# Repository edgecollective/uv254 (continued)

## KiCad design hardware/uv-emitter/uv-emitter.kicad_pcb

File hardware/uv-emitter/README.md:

# UV-Emitter

UV LED board: an Inolux IN-C35PPCTGU0 UV-C LED with its driver circuit.
Called **UV-LED-source** in the `uv-water` repository.

The driver is a current sink: an OPA4340 op-amp drives Q1 so that the
voltage across R2 (24.9 Ω) matches LED_DRIVE divided down by R3/R4 (100k/24.9k):
3.3 V on LED_DRIVE gives about 26 mA, and 2.5 V about 20 mA. From v0.5 the op-amp runs from 3.3 V, Q1 is an
MMBT3904 (a BSS138 fits the same pads), and the LED has its own 12 V supply.

The cable connector is a 6-pin JST PH (J2), with a 0.1" socket (J1) in
parallel:

| Pin | 1 | 2 | 3 | 4 | 5 | 6 |
|---|---|---|---|---|---|---|
| Signal | LED_CURRENT_MEASURE (`LED_CUR`) | LED_DISABLE (`LED_DIS`) | LED_DRIVE (`LED_DRV`) | +12V (LED supply) | 3V3 | GND |

LED_DISABLE high turns the LED off (Q2 grounds the setpoint). LED_CURRENT_MEASURE
is the voltage across R2: 0.5 V at 20 mA.

Open `uv-emitter.kicad_pro` in KiCad 10. Custom parts come from
[`lib/`](../../lib).

**[Download the KiCad files (zip)](https://github.com/edgecollective/uv254/archive/refs/heads/main.zip)**: the whole repository as it is on
`main`, because the board needs the shared `lib/` folder. This board is in
`hardware/uv-emitter/`.

<!-- render-images:start -->
<!-- Generated by scripts/render-images.sh. Edits between these markers are overwritten. -->

## Schematic

Click the image for the [PDF](docs/uv-emitter-schematic.pdf).

## Board layout

Copper and silkscreen. The back is mirrored, as seen from below.

| Front | Back |
|:---:|:---:|
|  |  |

## 3D view

| Front | Back |
|:---:|:---:|
|  |  |

Images of the current design, made with `scripts/render-images.sh uv-emitter`.
Re-run it after changing the board; see
[Updating the board images](../../README.md#updating-the-board-images).
<!-- render-images:end -->

## Revisions

| Version | Date | Status | Design | Fab files |
|---|---|---|---|---|
| v0.1 | 2024-03-11 | gerbers released | tag `uv-emitter/v0.1` | [`fab/v0.1`](fab/v0.1) |
| v0.2 | 2024-04-06 | gerbers released | tag `uv-emitter/v0.2` | [`fab/v0.2`](fab/v0.2) |
| v0.3 | 2024-08-19 | ordered from JLCPCB with detector v0.3 and control v0.1 | tag `uv-emitter/v0.3` | [`fab/v0.3`](fab/v0.3) |
| v0.2_A | 2026-06 to 2026-10 | design revision branched from v0.2, not fabricated | tag `uv-emitter/v0.2_A` | — |
| v0.4 | 2026-11-08 | gerbers released; derived from v0.2_A (5 V, 7 V LED supply, LED_ENABLE) | tag `uv-emitter/v0.4` | [`fab/v0.4`](fab/v0.4) |
| v0.5 | 2026-11-23 | gerbers released, then renumbered v0.6 with the set before ordering (same design) | tag `uv-emitter/v0.5` | [`fab/v0.5`](fab/v0.5) |
| **v0.6** | 2026-11-23 | **gerbers released**: 3.3 V, 12 V LED supply, MMBT3904 driver, LED_DISABLE; for UV-Control v0.6 | tag `uv-emitter/v0.6` | [`fab/v0.6`](fab/v0.6) |

Notes:

- **v0.3** has no `.kicad_pro`, because it was never committed upstream. Open
  `uv-emitter.kicad_pcb` or `.kicad_sch` directly at that tag.
- **v0.4** was called "v0.3" in `uv-water`. It was renumbered because v0.3 was
  already used by the 2024 JLCPCB order.
- **v0.4 has a pinout error on Q2**, the LED-disable switch. Its symbol was the
  through-hole 2N7000 (pin 1 source, 2 gate, 3 drain) on a SOT-23 footprint,
  where a 2N7002 or BSS138 has pin 1 gate, 2 source, 3 drain. With a SOT-23
  MOSFET fitted, Q2's gate is held at GND and LED_ENABLE drives its source: the
  LED can't be turned off that way, and driving LED_ENABLE high makes Q2's body
  diode conduct, raising the setpoint to about 2.7 V, which asks for about
  100 mA instead of 20 mA. On v0.4 boards, leave Q2 unfitted (or keep
  LED_ENABLE low) and turn the LED off with LED_DRIVE = 0. Fixed in v0.5.
- **v0.5** (in progress) moves to the system-wide 3.3 V supply:
  - op-amp supply 3.3 V instead of 5 V (connector pin 5); the LED gets its own
    12 V supply on pin 4 instead of 7.5 V, for more headroom over the LED's
    forward voltage
  - Q1 is an MMBT3904 NPN with a 1 kΩ base resistor (R1, was a 2N7002-type
    MOSFET with 49.9 Ω), so the 3.3 V op-amp has plenty of drive; a BSS138 fits
    the same pads
  - Q2 uses the 2N7002 symbol, which fixes the v0.4 pinout error
  - LED_ENABLE renamed LED_DISABLE, since high turns the LED off (behaviour
    unchanged)
  - board re-laid out

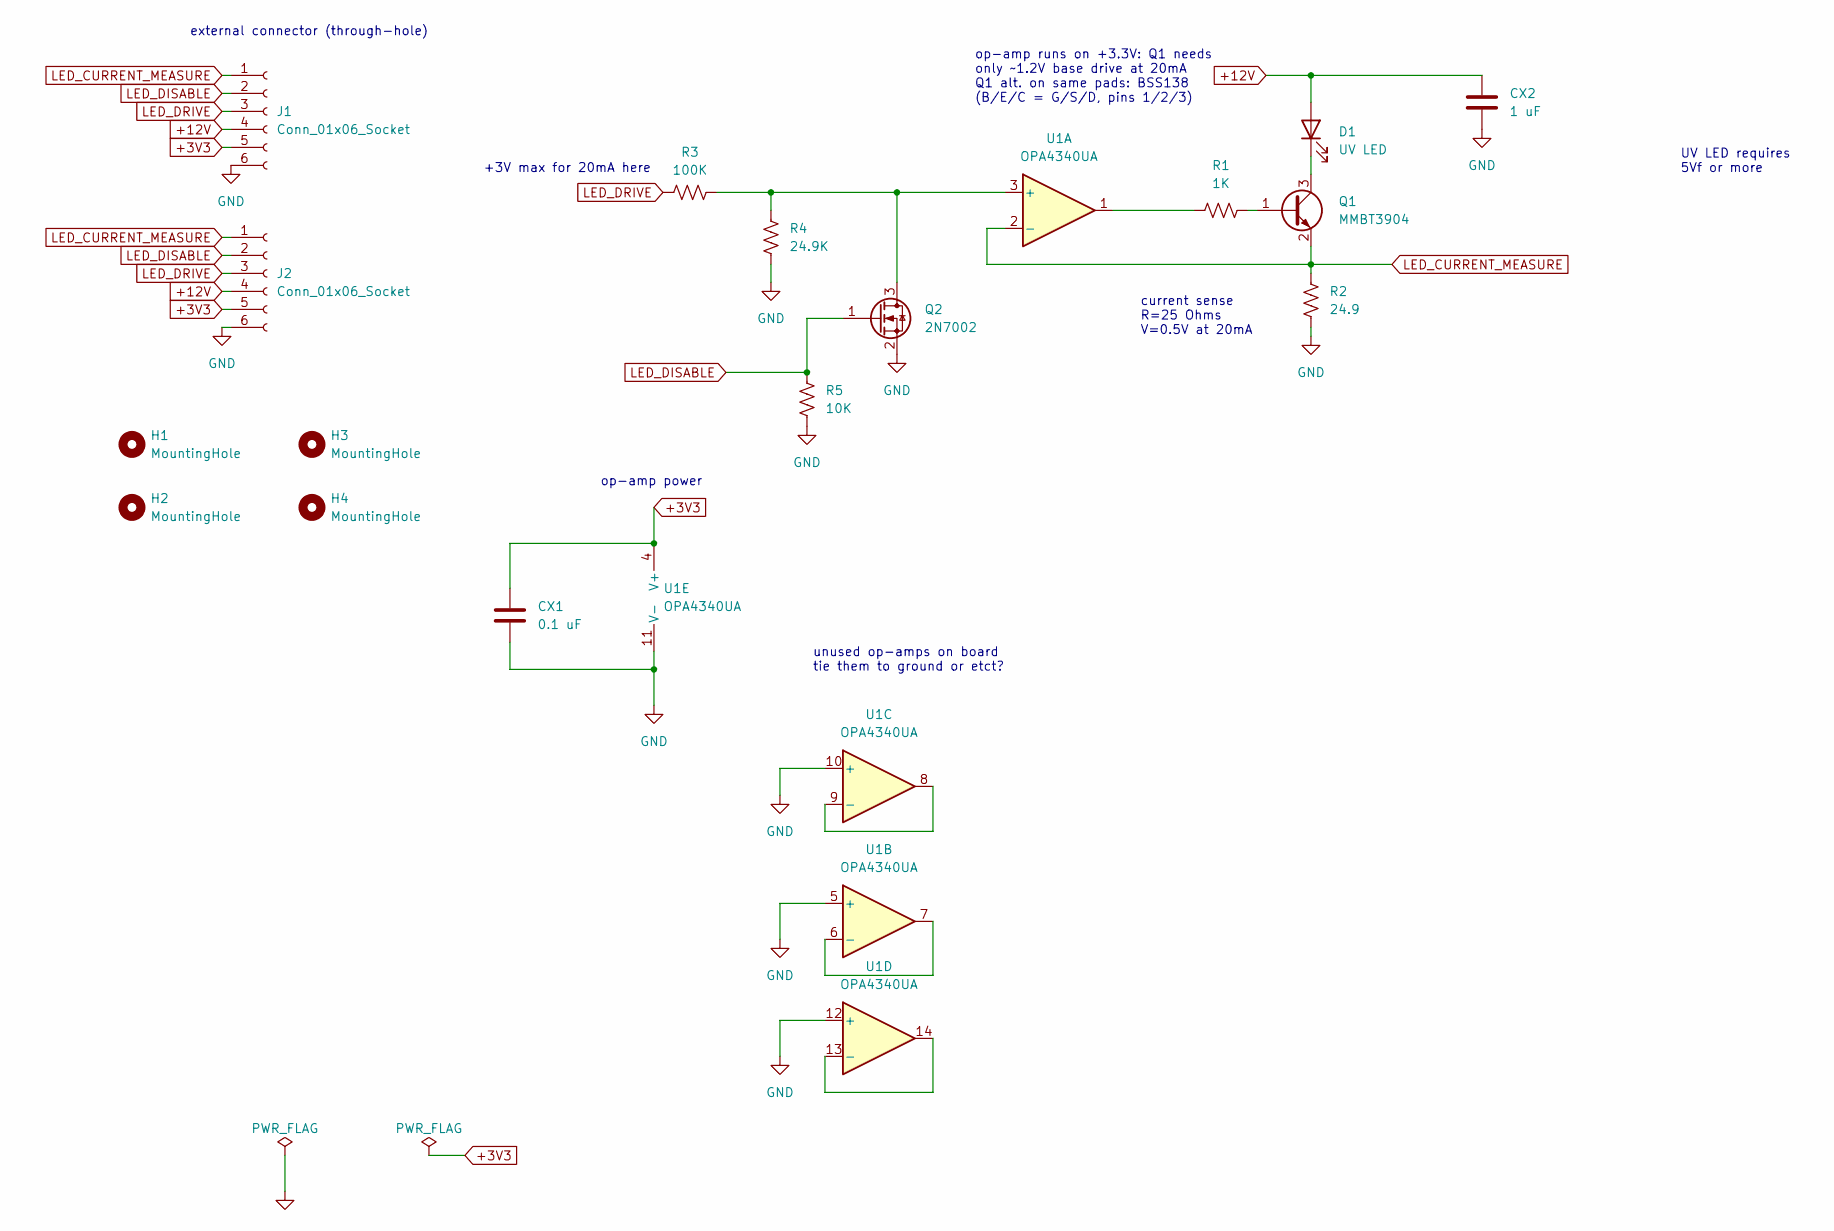
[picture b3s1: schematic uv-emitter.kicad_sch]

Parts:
CX1: 0.1 uF; C_0805_2012Metric_Pad1.18x1.45mm_HandSolder
CX2: 1 uF; C_0805_2012Metric_Pad1.18x1.45mm_HandSolder
D1: UV LED; LED_IN-C35PPCTGU0
H1, H2, H3, H4: MountingHole; MountingHole_3.2mm_M3
J1: Conn_01x06_Socket; PinSocket_1x06_P2.54mm_Vertical
J2: Conn_01x06_Socket; JST_PH_B6B-PH-K_1x06_P2.00mm_Vertical
Q1: MMBT3904; SOT-23
Q2: 2N7002; SOT-23
R1: 1K; R_0805_2012Metric_Pad1.20x1.40mm_HandSolder
R2: 24.9; R_0805_2012Metric_Pad1.20x1.40mm_HandSolder
R3: 100K; R_0805_2012Metric_Pad1.20x1.40mm_HandSolder
R4: 24.9K; R_0805_2012Metric_Pad1.20x1.40mm_HandSolder
R5: 10K; R_0805_2012Metric_Pad1.20x1.40mm_HandSolder
U1: OPA4340UA; SOIC-14_3.9x8.7mm_P1.27mm

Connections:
+3V3: CX1.1, J1.5, J2.5, U1.4 (V+)
+12V: CX2.1, D1.2 (A), J1.4, J2.4
GND: CX1.2, CX2.2, J1.6, J2.6, Q2.2 (S), R2.1, R4.1, R5.1, U1.5 (+), U1.10 (+), U1.11 (V-), U1.12 (+)
LED_CURRENT_MEASURE: J1.1, J2.1, Q1.2 (E), R2.2, U1.2 (-)
LED_DISABLE: J1.2, J2.2, Q2.1 (G), R5.2
LED_DRIVE: J1.3, J2.3, R3.1
unnamed: D1.1 (K), Q1.3 (C)
unnamed: Q1.1 (B), R1.2
unnamed: Q2.3 (D), R3.2, R4.2, U1.3 (+)
unnamed: R1.1, U1.1
unnamed: U1.6 (-), U1.7
unnamed: U1.8, U1.9 (-)
unnamed: U1.13 (-), U1.14

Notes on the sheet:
+3V max for 20mA here
UV LED requires 5Vf or more
external connector (through-hole)
op-amp runs on +3.3V: Q1 needs only ~1.2V base drive at 20mA Q1 alt. on same pads: BSS138 (B/E/C = G/S/D, pins 1/2/3)
current sense R=25 Ohms V=0.5V at 20mA
unused op-amps on board tie them to ground or etct?
op-amp power

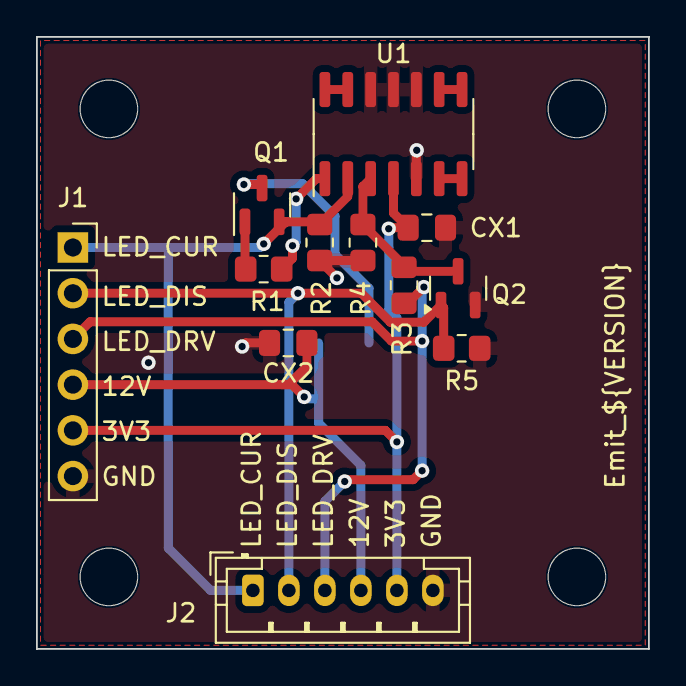
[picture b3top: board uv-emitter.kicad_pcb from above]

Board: 2 copper layers, 34.0 x 34.0 mm, 17 parts (1 on the bottom side), 13 nets.

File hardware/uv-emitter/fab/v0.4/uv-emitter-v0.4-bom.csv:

"Refs","Value","Footprint","Qty","DNP","Description"
"CX1","0.1 uF","Capacitor_SMD:C_0805_2012Metric_Pad1.18x1.45mm_HandSolder","1","","Unpolarized capacitor"
"CX2","1 uF","Capacitor_SMD:C_0805_2012Metric_Pad1.18x1.45mm_HandSolder","1","","Unpolarized capacitor"
"D1","UV LED","uv254:LED_IN-C35PPCTGU0","1","",""
"H1,H2,H3,H4","MountingHole","MountingHole:MountingHole_3.2mm_M3","4","","Mounting Hole without connection"
"J1","Conn_01x06_Socket","Connector_PinSocket_2.54mm:PinSocket_1x06_P2.54mm_Vertical","1","","Generic connector, single row, 01x06, script generated"
"J2","Conn_01x06_Socket","Connector_JST:JST_PH_B6B-PH-K_1x06_P2.00mm_Vertical","1","","Generic connector, single row, 01x06, script generated"
"Q1,Q2","2N7000","Package_TO_SOT_SMD:SOT-23","2","","0.2A Id, 200V Vds, N-Channel MOSFET, 2.6V Logic Level, TO-92"
"R1","49.9","Resistor_SMD:R_0805_2012Metric_Pad1.20x1.40mm_HandSolder","1","",""
"R2","24.9","Resistor_SMD:R_0805_2012Metric_Pad1.20x1.40mm_HandSolder","1","",""
"R3","100K","Resistor_SMD:R_0805_2012Metric_Pad1.20x1.40mm_HandSolder","1","",""
"R4","24.9K","Resistor_SMD:R_0805_2012Metric_Pad1.20x1.40mm_HandSolder","1","",""
"R5","10K","Resistor_SMD:R_0805_2012Metric_Pad1.20x1.40mm_HandSolder","1","",""
"U1","OPA4340UA","Package_SO:SOIC-14_3.9x8.7mm_P1.27mm","1","","Quad Single-Supply, Rail-to-Rail Operational Amplifier, MicroAmplifier Series, SOIC-14"

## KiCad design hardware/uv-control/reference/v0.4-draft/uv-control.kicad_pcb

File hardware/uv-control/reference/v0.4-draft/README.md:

# UV-Control v0.4: first draft (reference only)

The first v0.4 control-board draft, kept for reference when the board was
restarted from Rook v0.4 on 2026-11-13. It is the state of `main` at commit
`87ac380` plus the edits made on 2026-11-13 before the restart (schematic tidy-up
and a start on the PCB).

- `uv-control.kicad_sch`, `.kicad_pcb`, `.kicad_pro`: the KiCad project. Opens
  on its own; library tables point at the shared `lib/`. Its Pro Micro symbol
  (`ProMicro_nRF52840`) is embedded in the schematic; the matching footprint is
  only in the PCB and in git history.
- `uv-control-v0.4-draft-schematic.pdf`: the schematic.
- `v0.4-design.md`: the design notes for this draft (pin map, LMR62014 8 V boost,
  checks before building).

The ADS1115 block, the detector/emitter JST connectors and the LED_DRIVE parts
were carried over into the restarted board. The LMR62014 boost was not.

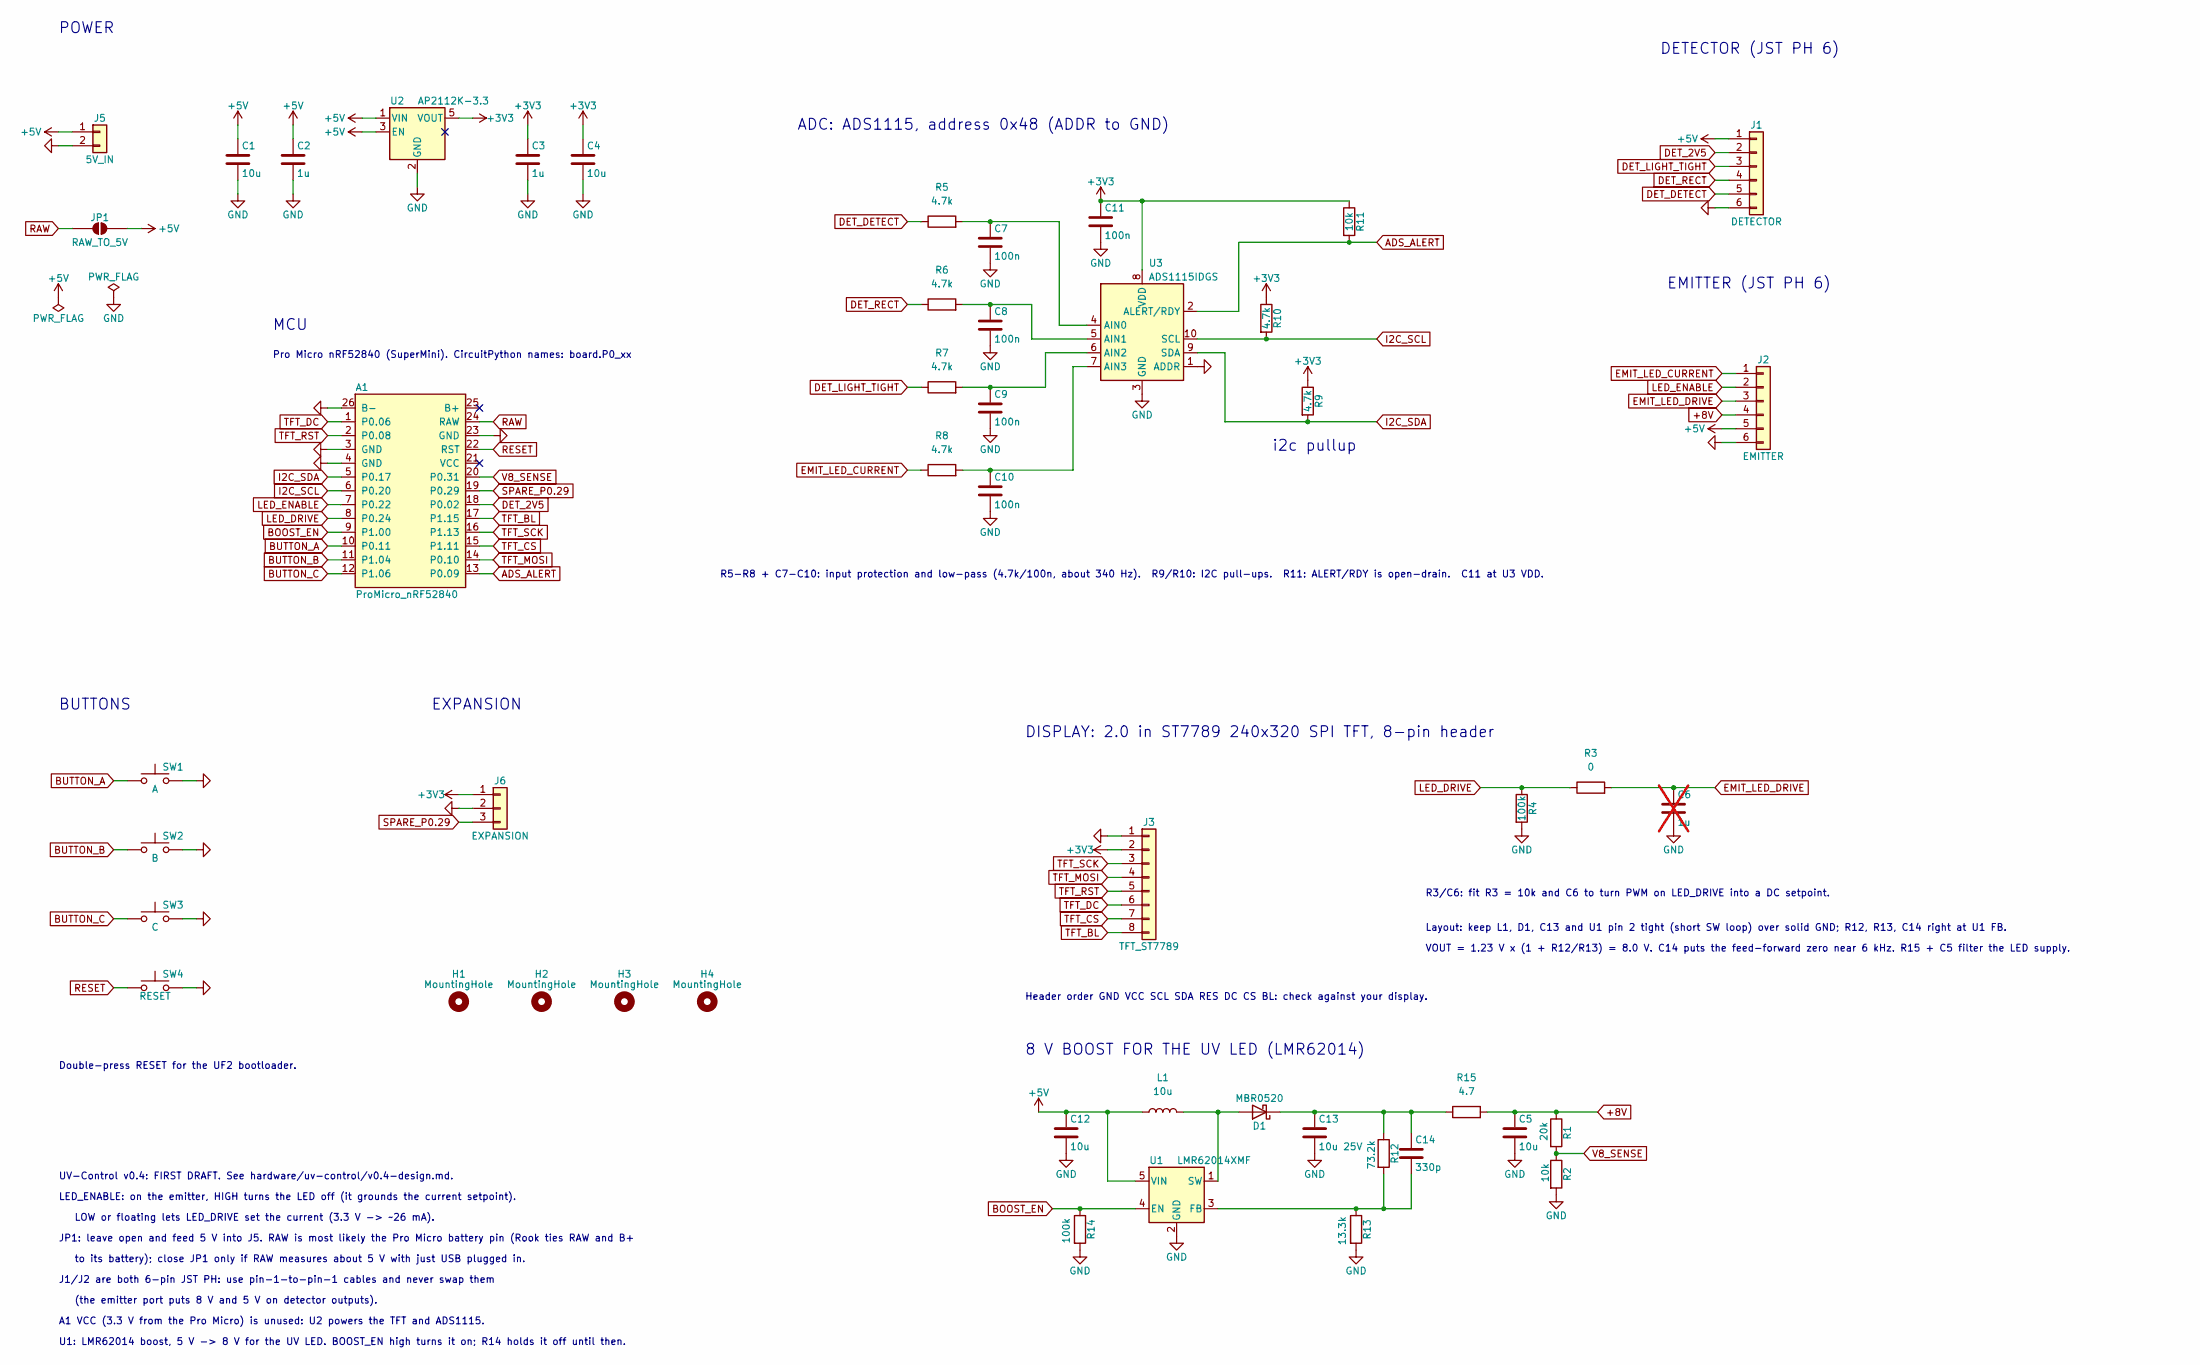
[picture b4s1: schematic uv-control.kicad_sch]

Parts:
A1: ProMicro_nRF52840
C1, C4, C5, C12: 10u; C_0805_2012Metric
C2, C3: 1u; C_0805_2012Metric
C6: 1u; C_0805_2012Metric; not fitted
C7, C8, C9, C10, C11: 100n; C_0805_2012Metric
C13: 10u 25V; C_1206_3216Metric
C14: 330p; C_0805_2012Metric
D1: MBR0520; D_SOD-123
H1, H2, H3, H4: MountingHole; MountingHole_3.2mm_M3
J1: DETECTOR; JST_PH_B6B-PH-K_1x06_P2.00mm_Vertical
J2: EMITTER; JST_PH_B6B-PH-K_1x06_P2.00mm_Vertical
J3: TFT_ST7789; PinHeader_1x08_P2.54mm_Vertical
J5: 5V_IN; JST_PH_B2B-PH-K_1x02_P2.00mm_Vertical
J6: EXPANSION; PinHeader_1x03_P2.54mm_Vertical
JP1: RAW_TO_5V; SolderJumper-2_P1.3mm_Open_Pad1.0x1.5mm
L1: 10u; L_Bourns-SRN4018
R1: 20k; R_0805_2012Metric
R2, R11: 10k; R_0805_2012Metric
R3: 0; R_0805_2012Metric
R4, R14: 100k; R_0805_2012Metric
R5, R6, R7, R8, R9, R10: 4.7k; R_0805_2012Metric
R12: 73.2k; R_0805_2012Metric
R13: 13.3k; R_0805_2012Metric
R15: 4.7; R_0805_2012Metric
SW1: A; SW_Tactile_SPST_Angled_PTS645Vx31-2LFS
SW2: B; SW_Tactile_SPST_Angled_PTS645Vx31-2LFS
SW3: C; SW_Tactile_SPST_Angled_PTS645Vx31-2LFS
SW4: RESET; SW_Tactile_SPST_Angled_PTS645Vx31-2LFS
U1: LMR62014XMF; SOT-23-5
U2: AP2112K-3.3; SOT-23-5
U3: ADS1115IDGS; TSSOP-10_3x3mm_P0.5mm

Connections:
+3V3: C3.1, C4.1, C11.1, J3.2, J6.1, R9.1, R10.1, R11.1, U2.5 (VOUT), U3.8 (VDD)
+5V: C1.1, C2.1, C12.1, J1.1, J2.5, J5.1, JP1.2 (B), L1.1, U1.5 (VIN), U2.1 (VIN), U2.3 (EN)
+8V: C5.1, J2.4, R1.1, R15.2
ADS_ALERT: A1.13 (P0.09), R11.2, U3.2 (ALERT/RDY)
BOOST_EN: A1.9 (P1.00), R14.1, U1.4 (EN)
BUTTON_A: A1.10 (P0.11), SW1.1
BUTTON_B: A1.11 (P1.04), SW2.1
BUTTON_C: A1.12 (P1.06), SW3.1
DET_2V5: A1.18 (P0.02), J1.2
DET_DETECT: J1.5, R5.1
DET_LIGHT_TIGHT: J1.3, R7.1
DET_RECT: J1.4, R6.1
EMIT_LED_CURRENT: J2.1, R8.1
EMIT_LED_DRIVE: C6.1, J2.3, R3.2
GND: A1.3 (GND), A1.4 (GND), A1.23 (GND), A1.26 (B-), C1.2, C2.2, C3.2, C4.2, C5.2, C6.2, C7.2, C8.2, C9.2, C10.2, C11.2, C12.2, C13.2, J1.6, J2.6, J3.1, J5.2, J6.2, R2.2, R4.2, R13.2, R14.2, SW1.2, SW2.2, SW3.2, SW4.2, U1.2 (GND), U2.2 (GND), U3.1 (ADDR), U3.3 (GND)
I2C_SCL: A1.6 (P0.20), R10.2, U3.10 (SCL)
I2C_SDA: A1.5 (P0.17), R9.2, U3.9 (SDA)
LED_DRIVE: A1.8 (P0.24), R3.1, R4.1
LED_ENABLE: A1.7 (P0.22), J2.2
unnamed: D1.2 (A), L1.2, U1.1 (SW)
unnamed: C13.1, C14.1, D1.1 (K), R12.1, R15.1
unnamed: C14.2, R12.2, R13.1, U1.3 (FB)
unnamed: C7.1, R5.2, U3.4 (AIN0)
unnamed: C8.1, R6.2, U3.5 (AIN1)
unnamed: C9.1, R7.2, U3.6 (AIN2)
unnamed: C10.1, R8.2, U3.7 (AIN3)
RAW: A1.24 (RAW), JP1.1 (A)
RESET: A1.22 (RST), SW4.1
SPARE_P0.29: A1.19 (P0.29), J6.3
TFT_BL: A1.17 (P1.15), J3.8
TFT_CS: A1.15 (P1.11), J3.7
TFT_DC: A1.1 (P0.06), J3.6
TFT_MOSI: A1.14 (P0.10), J3.4
TFT_RST: A1.2 (P0.08), J3.5
TFT_SCK: A1.16 (P1.13), J3.3
V8_SENSE: A1.20 (P0.31), R1.2, R2.1

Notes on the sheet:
UV-Control v0.4: FIRST DRAFT. See hardware/uv-control/v0.4-design.md.
VOUT = 1.23 V x (1 + R12/R13) = 8.0 V. C14 puts the feed-forward zero near 6 kHz. R15 + C5 filter the LED supply.
Double-press RESET for the UF2 bootloader.
POWER
Header order GND VCC SCL SDA RES DC CS BL: check against your display.
to its battery); close JP1 only if RAW measures about 5 V with just USB plugged in.
EMITTER (JST PH 6)
(the emitter port puts 8 V and 5 V on detector outputs).
ADC: ADS1115, address 0x48 (ADDR to GND)
BUTTONS
Pro Micro nRF52840 (SuperMini). CircuitPython names: board.P0_xx
R5-R8 + C7-C10: input protection and low-pass (4.7k/100n, about 340 Hz). R9/R10: I2C pull-ups. R11: ALERT/RDY is open-drain. C11 at U3 VDD.
A1 VCC (3.3 V from the Pro Micro) is unused: U2 powers the TFT and ADS1115.
i2c pullup
DETECTOR (JST PH 6)
R3/C6: fit R3 = 10k and C6 to turn PWM on LED_DRIVE into a DC setpoint.
LOW or floating lets LED_DRIVE set the current (3.3 V -> ~26 mA).
Layout: keep L1, D1, C13 and U1 pin 2 tight (short SW loop) over solid GND; R12, R13, C14 right at U1 FB.
JP1: leave open and feed 5 V into J5. RAW is most likely the Pro Micro battery pin (Rook ties RAW and B+
EXPANSION
LED_ENABLE: on the emitter, HIGH turns the LED off (it grounds the current setpoint).
J1/J2 are both 6-pin JST PH: use pin-1-to-pin-1 cables and never swap them
MCU
U1: LMR62014 boost, 5 V -> 8 V for the UV LED. BOOST_EN high turns it on; R14 holds it off until then.
8 V BOOST FOR THE UV LED (LMR62014)
DISPLAY: 2.0 in ST7789 240x320 SPI TFT, 8-pin header

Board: 2 copper layers, 49 parts (0 on the bottom side), 36 nets, no tracks yet.

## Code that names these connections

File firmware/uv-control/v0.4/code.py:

# SPDX-License-Identifier: MIT
"""UV-Control v0.4 bring-up test.

Reads the detector and emitter signals through the ADS1115, switches the UV LED
and shows the readings on the ST7789 TFT and the USB serial console.

Board: SuperMini nRF52840 (CircuitPython's "SuperMini NRF52840" build).
Wiring: hardware/uv-control/v0.4-design.md (pin map).

Buttons:
  A  LED on/off (manual)
  B  measure: dark, LED on, dark again; shows light minus dark per channel
  C  use the last measurement as the blank, so later ones show absorbance
"""
import math
import time

import analogio
import board
import busio
import digitalio
import displayio
import terminalio
from adafruit_ads1x15 import ADS1115, AnalogIn, ads1x15
from adafruit_display_text import label
from adafruit_st7789 import ST7789
from fourwire import FourWire

# --- Pins: keep in step with the schematic and v0.4-design.md
TFT_SCK, TFT_MOSI, TFT_CS = board.P1_13, board.P0_10, board.P1_11
TFT_DC, TFT_RST, TFT_BL = board.P0_06, board.P0_08, board.P1_15
I2C_SDA, I2C_SCL = board.P0_17, board.P0_20
LED_DISABLE = board.P0_22   # emitter: HIGH forces the LED off, LOW lets LED_DRIVE set it
LED_DRIVE = board.P0_24    # emitter current setpoint: HIGH (3.3 V) gives about 26 mA
BOOST_EN = board.P1_00     # U1 (LMR62014) enable: HIGH turns the 8 V LED supply on
BUTTONS = (board.P0_11, board.P1_04, board.P1_06)   # A, B, C to GND
V8_SENSE = board.P0_31     # 8 V LED supply through a 20k/10k divider
DET_1V8 = board.P0_02      # the detector's 1.8 V reference

SENSE_OHMS = 24.9          # emitter current-sense resistor (R2 on the emitter)
SETTLE_S = 0.05            # wait after switching the LED before reading
SAMPLES = 8                # readings averaged per channel


def output(pin, value):
    io = digitalio.DigitalInOut(pin)
    io.switch_to_output(value=value)
    return io


# LED off before anything else
led_disable = output(LED_DISABLE, True)
led_drive = output(LED_DRIVE, False)
boost_en = output(BOOST_EN, True)
led_is_on = False


def set_led(on):
    global led_is_on
    led_drive.value = on
    led_disable.value = not on
    led_is_on = on


buttons = []
for pin in BUTTONS:
    b = digitalio.DigitalInOut(pin)
    b.switch_to_input(pull=digitalio.Pull.UP)
    buttons.append(b)
last_state = [True] * len(buttons)


def pressed():
    """Index of a button that was just pressed, or None."""
    for i, b in enumerate(buttons):
        down = not b.value
        if down and last_state[i]:
            last_state[i] = False
            return i
        if not down:
            last_state[i] = True
    return None


# --- ADC
i2c = busio.I2C(I2C_SCL, I2C_SDA)
ads = ADS1115(i2c)          # address 0x48 (ADDR to GND)
ads.gain = 1                # +/-4.096 V full scale
CHANNELS = (
    ("detect", AnalogIn(ads, ads1x15.Pin.A0)),
    ("rect", AnalogIn(ads, ads1x15.Pin.A1)),
    ("light-tight", AnalogIn(ads, ads1x15.Pin.A2)),
    ("LED sense", AnalogIn(ads, ads1x15.Pin.A3)),
)
v8 = analogio.AnalogIn(V8_SENSE)
v1v8 = analogio.AnalogIn(DET_1V8)


def read_all():
    sums = [0.0] * len(CHANNELS)
    for _ in range(SAMPLES):
        for i, (_, ch) in enumerate(CHANNELS):
            sums[i] += ch.voltage
    return [s / SAMPLES for s in sums]


def internal_volts(adc, scale=1.0):
    return adc.value / 65535 * adc.reference_voltage * scale


# --- Display: 2.0" 240x320 ST7789, used in landscape
displayio.release_displays()
spi = busio.SPI(TFT_SCK, MOSI=TFT_MOSI)
bus = FourWire(spi, command=TFT_DC, chip_select=TFT_CS, reset=TFT_RST, baudrate=24_000_000)
display = ST7789(bus, width=320, height=240, rotation=90, backlight_pin=TFT_BL)
screen = displayio.Group()
display.root_group = screen


def text_line(y, color=0xFFFFFF, scale=2):
    t = label.Label(terminalio.FONT, text="", color=color, scale=scale, x=6, y=y)
    screen.append(t)
    return t


title = text_line(12, 0x66CCFF)
title.text = "UV-Control v0.4"
rows = [text_line(44 + 24 * i) for i in range(len(CHANNELS))]
status = text_line(150, 0xFFCC00)
result = text_line(184, 0x99FF99)
hint = text_line(226, 0x888888, scale=1)
hint.text = "A: LED on/off   B: measure   C: set blank"

blank = None
last = None


def measure():
    """Light minus dark for each channel, with the LED off before and after."""
    set_led(False)
    time.sleep(SETTLE_S)
    dark1 = read_all()
    set_led(True)
    time.sleep(SETTLE_S)
    light = read_all()
    set_led(False)
    time.sleep(SETTLE_S)
    dark2 = read_all()
    return [l - (a + b) / 2 for l, a, b in zip(light, dark1, dark2)], light


print("time_s,detect_V,rect_V,light_tight_V,led_sense_V,led_on")
while True:
    button = pressed()
    if button == 0:
        set_led(not led_is_on)
    elif button == 1:
        last, light = measure()
        led_mA = light[3] / SENSE_OHMS * 1000
        line = "signal %.4f V  LED %.1f mA" % (last[0], led_mA)
        if blank and last[0] > 0 and blank[0] > 0:
            line = "A = %.4f  LED %.1f mA" % (-math.log10(last[0] / blank[0]), led_mA)
        result.text = line
        print("measure," + ",".join("%.5f" % v for v in last))
    elif button == 2 and last:
        blank = last
        result.text = "blank set: %.4f V" % blank[0]

    volts = read_all()
    for row, (name, _), v in zip(rows, CHANNELS, volts):
        row.text = "%-11s %7.4f V" % (name, v)
    status.text = "LED %s  8V %.2f V  1V8 %.3f V" % (
        "ON " if led_is_on else "off", internal_volts(v8, 3.0), internal_volts(v1v8))
    print("%.2f,%s,%d" % (time.monotonic(), ",".join("%.5f" % v for v in volts), led_is_on))
    time.sleep(0.2)
